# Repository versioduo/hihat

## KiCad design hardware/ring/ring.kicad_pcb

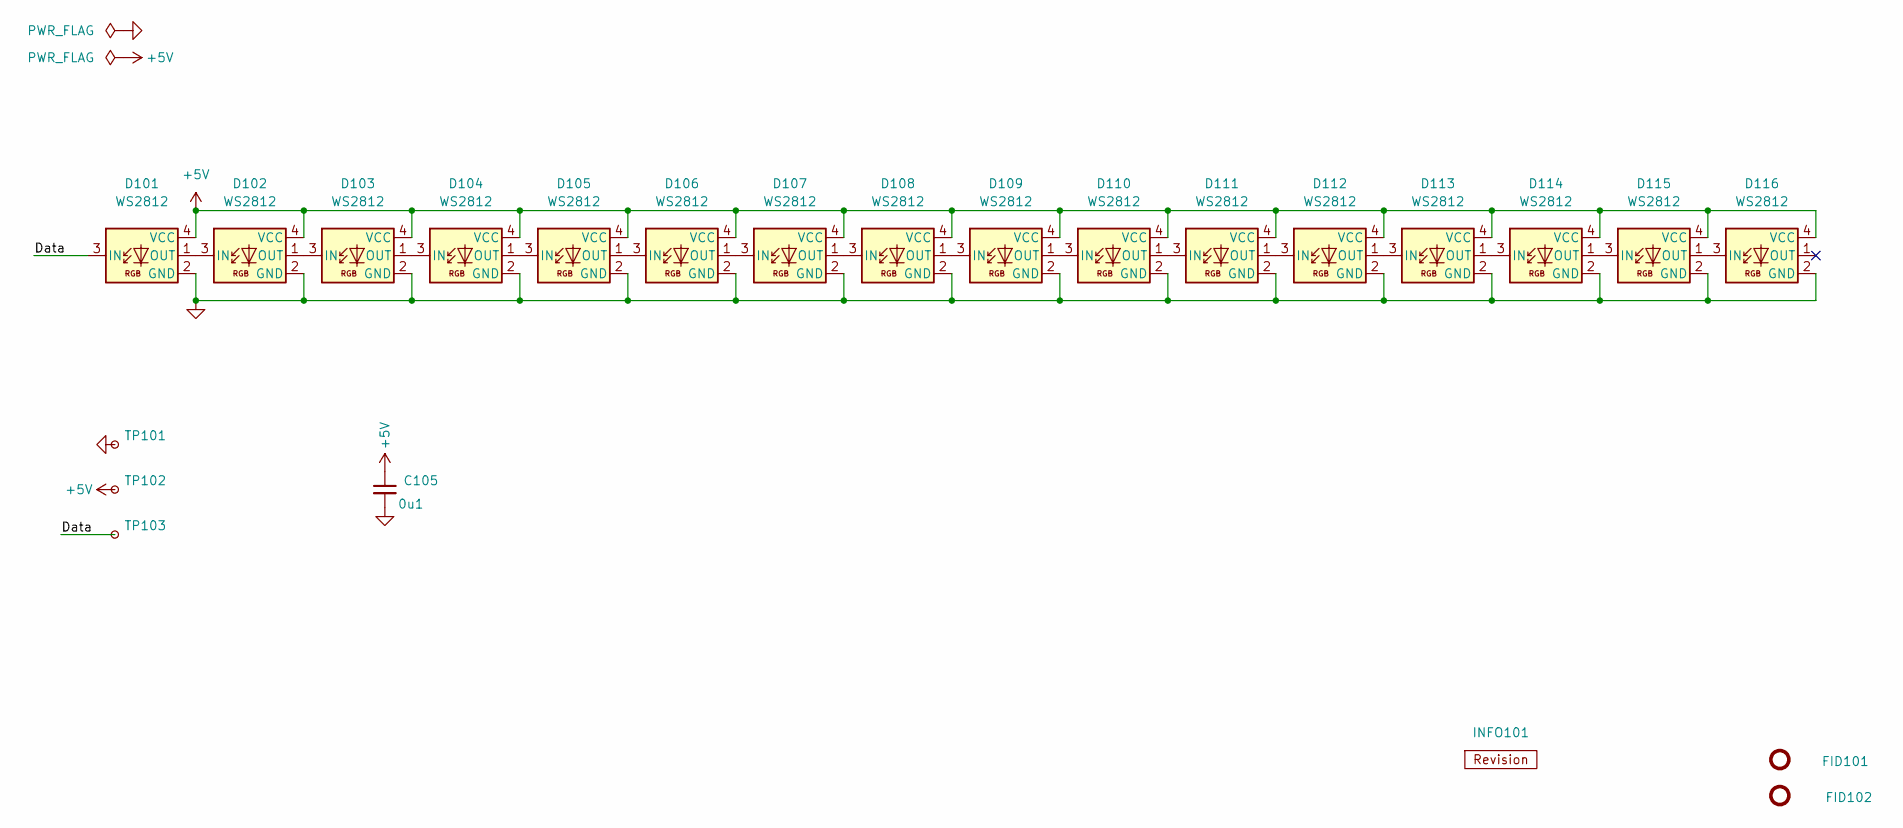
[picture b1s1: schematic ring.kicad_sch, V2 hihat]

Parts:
C105: 0u1; C_1608; Rating 50V; Mouser 810-CGA3E2X7R1H104MA
D101, D102, D103, D104, D105, D106, D107, D108, D109, D110, D111, D112, D113, D114, D115, D116: WS2812; WS2812-2020; LCSC C965555
FID101, FID102: Fiducial_Paste; Fiducial_0.5mm_Mask1mm_Paste
INFO101: Revision
TP101, TP102, TP103: TestPoint_THTPad_D1.0mm_Drill0.5mm

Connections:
+5V: C105.1, D101.4 (VCC), D102.4 (VCC), D103.4 (VCC), D104.4 (VCC), D105.4 (VCC), D106.4 (VCC), D107.4 (VCC), D108.4 (VCC), D109.4 (VCC), D110.4 (VCC), D111.4 (VCC), D112.4 (VCC), D113.4 (VCC), D114.4 (VCC), D115.4 (VCC), D116.4 (VCC), TP102.1
/Data: D101.3 (IN), TP103.1
GND: C105.2, D101.2 (GND), D102.2 (GND), D103.2 (GND), D104.2 (GND), D105.2 (GND), D106.2 (GND), D107.2 (GND), D108.2 (GND), D109.2 (GND), D110.2 (GND), D111.2 (GND), D112.2 (GND), D113.2 (GND), D114.2 (GND), D115.2 (GND), D116.2 (GND), TP101.1
unnamed: D101.1 (OUT), D102.3 (IN)
unnamed: D102.1 (OUT), D103.3 (IN)
unnamed: D103.1 (OUT), D104.3 (IN)
unnamed: D104.1 (OUT), D105.3 (IN)
unnamed: D105.1 (OUT), D106.3 (IN)
unnamed: D106.1 (OUT), D107.3 (IN)
unnamed: D107.1 (OUT), D108.3 (IN)
unnamed: D108.1 (OUT), D109.3 (IN)
unnamed: D109.1 (OUT), D110.3 (IN)
unnamed: D110.1 (OUT), D111.3 (IN)
unnamed: D111.1 (OUT), D112.3 (IN)
unnamed: D112.1 (OUT), D113.3 (IN)
unnamed: D113.1 (OUT), D114.3 (IN)
unnamed: D114.1 (OUT), D115.3 (IN)
unnamed: D115.1 (OUT), D116.3 (IN)

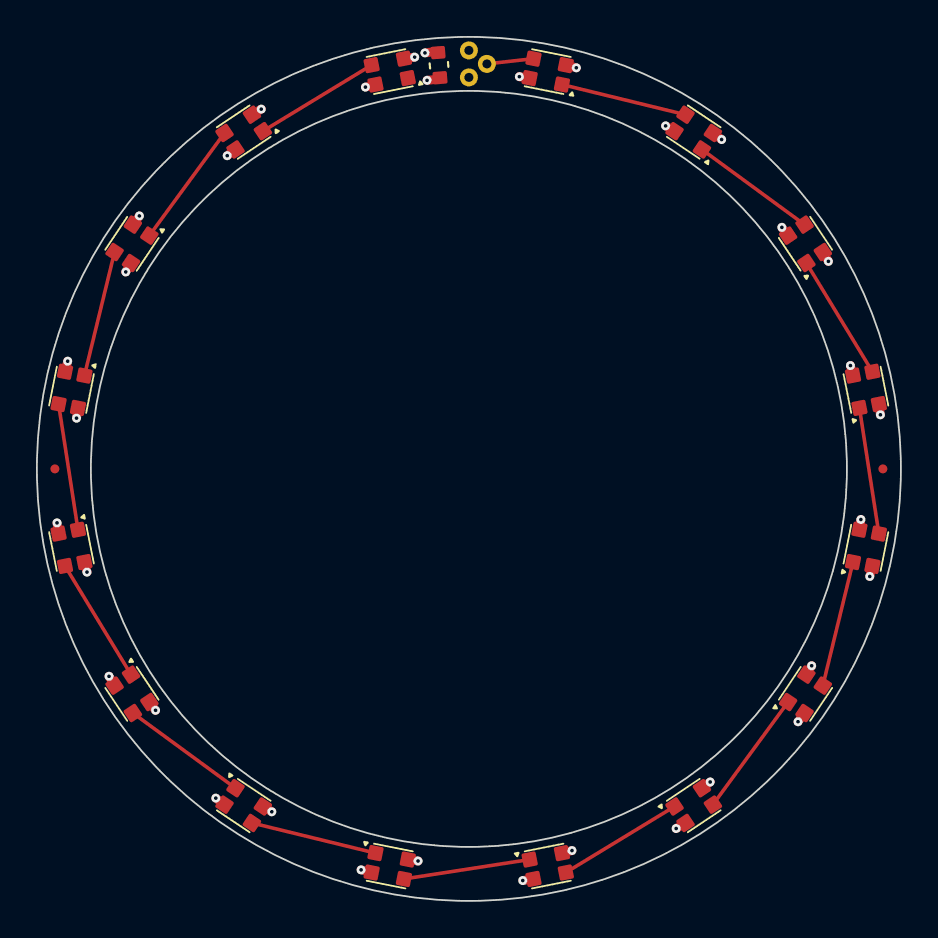
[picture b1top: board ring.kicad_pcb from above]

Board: 2 copper layers, 48.0 x 48.0 mm, 23 parts (1 on the bottom side), 18 nets.

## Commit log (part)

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2026-05-11 Import
2026-05-17 Export 16 MIDI ports
2026-06-21 Update MIDI API
2026-06-23 Update V2Link API
